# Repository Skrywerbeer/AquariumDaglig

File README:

# AquariumDaglig
This is my project for a switched solar day light. Unfortunatly I blew up my remaining LEDs so the firmware has stalled at this working version.
## Theory of Operation
TCB0 is configured in single-shot mode, the start of which is triggered by AC0's output via the event system.
When TCB0 is triggered PA6 is driven low, turning off the MOSFET allowing the inductor current to circulate
through the schottky diode and the LED string; resetting the inductor. In the main loop the PV voltage is monitored
based on it's value the reference for AC0 is either increased or decreased setting the peak inductor current.

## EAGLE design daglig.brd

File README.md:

# AquariumDaglig
This is my project for a switched solar day light. Unfortunatly I blew up my remaining LEDs so the firmware has stalled at this working version.

## Theory of Operation
TCB0 is configured in single-shot mode, the start of which is triggered by AC0's output via the event system.
When TCB0 is triggered PA6 is driven low, turning off the MOSFET allowing the inductor current to circulate
through the schottky diode and the LED string; resetting the inductor. In the main loop the PV voltage is monitored
based on it's value the reference for AC0 is either increased or decreased setting the peak inductor current.

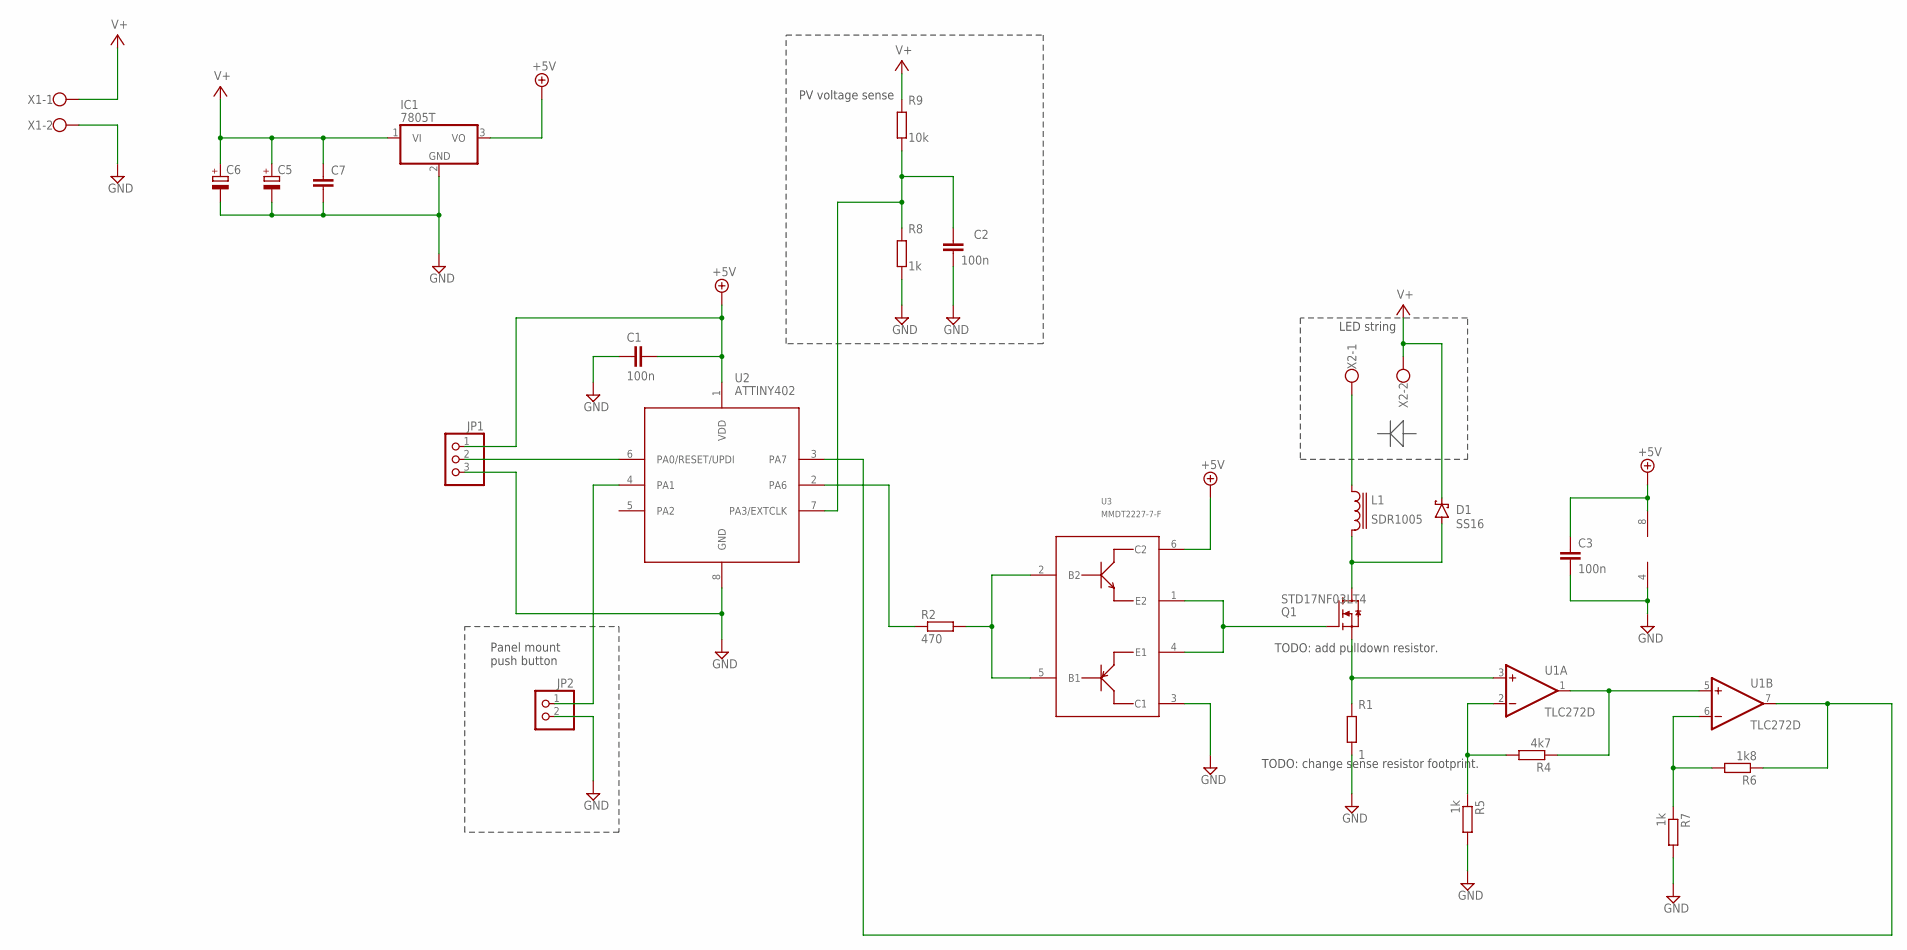
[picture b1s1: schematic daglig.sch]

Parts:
C1, C2, C3: 100n; C0805
C5, C6: CPOL-EUE5-10.5; E5-10,5
C7: C-EUC0805; C0805
D1: SS16; DO214AC
IC1: 7805T; TO220H
JP1: PINHD-1X3; 1X03
JP2: PINHD-1X2; 1X02
L1: SDR1005
Q1: STD17NF03LT4; TO252
R1: 1; R2512
R2: 470; R0805
R4: 4k7; R0805
R5, R7, R8: 1k; R0805
R6: 1k8; R0805
R9: 10k; R0805
U1: TLC272D; SO08
U2: ATTINY402; SO8
U3: MMDT2227-7-F; SOT363_PHILIPS
X1, X2: W237-102

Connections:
+5V: C1.2, C3.1, IC1.3 (VO), JP1.1, U1.8 (V+), U2.1 (VDD), U3.6 (C2)
GND: C1.1, C2.2, C3.2, C5.-, C6.-, C7.2, IC1.2 (GND), JP1.3, JP2.2, R1.1, R5.2, R7.2, R8.1, U1.4 (V-), U2.8 (GND), U3.3 (C1), X1.2
unnamed: Q1.1 (G), U3.1 (E2), U3.4 (E1)
unnamed: D1.A, L1.2, Q1.3 (D)
unnamed: R2.2, U3.2 (B2), U3.5 (B1)
unnamed: R2.1, U2.2 (PA6)
unnamed: Q1.2 (S), R1.2, U1.3 (+IN)
unnamed: R4.1, U1.1 (OUT), U1.5 (+IN)
unnamed: R6.1, U1.7 (OUT), U2.3 (PA7)
unnamed: R6.2, R7.1, U1.6 (-IN)
unnamed: R4.2, R5.1, U1.2 (-IN)
unnamed: L1.1, X2.1
unnamed: JP1.2, U2.6 (PA0/RESET/UPDI)
unnamed: C2.1, R8.2, R9.1, U2.7 (PA3/EXTCLK)
unnamed: JP2.1, U2.4 (PA1)
V+: C5.+, C6.+, C7.1, D1.C, IC1.1 (VI), R9.2, X1.1, X2.2

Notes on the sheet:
LED string
PV voltage sense
Panel mount push button
TODO: add pulldown resistor.
TODO: change sense resistor footprint.

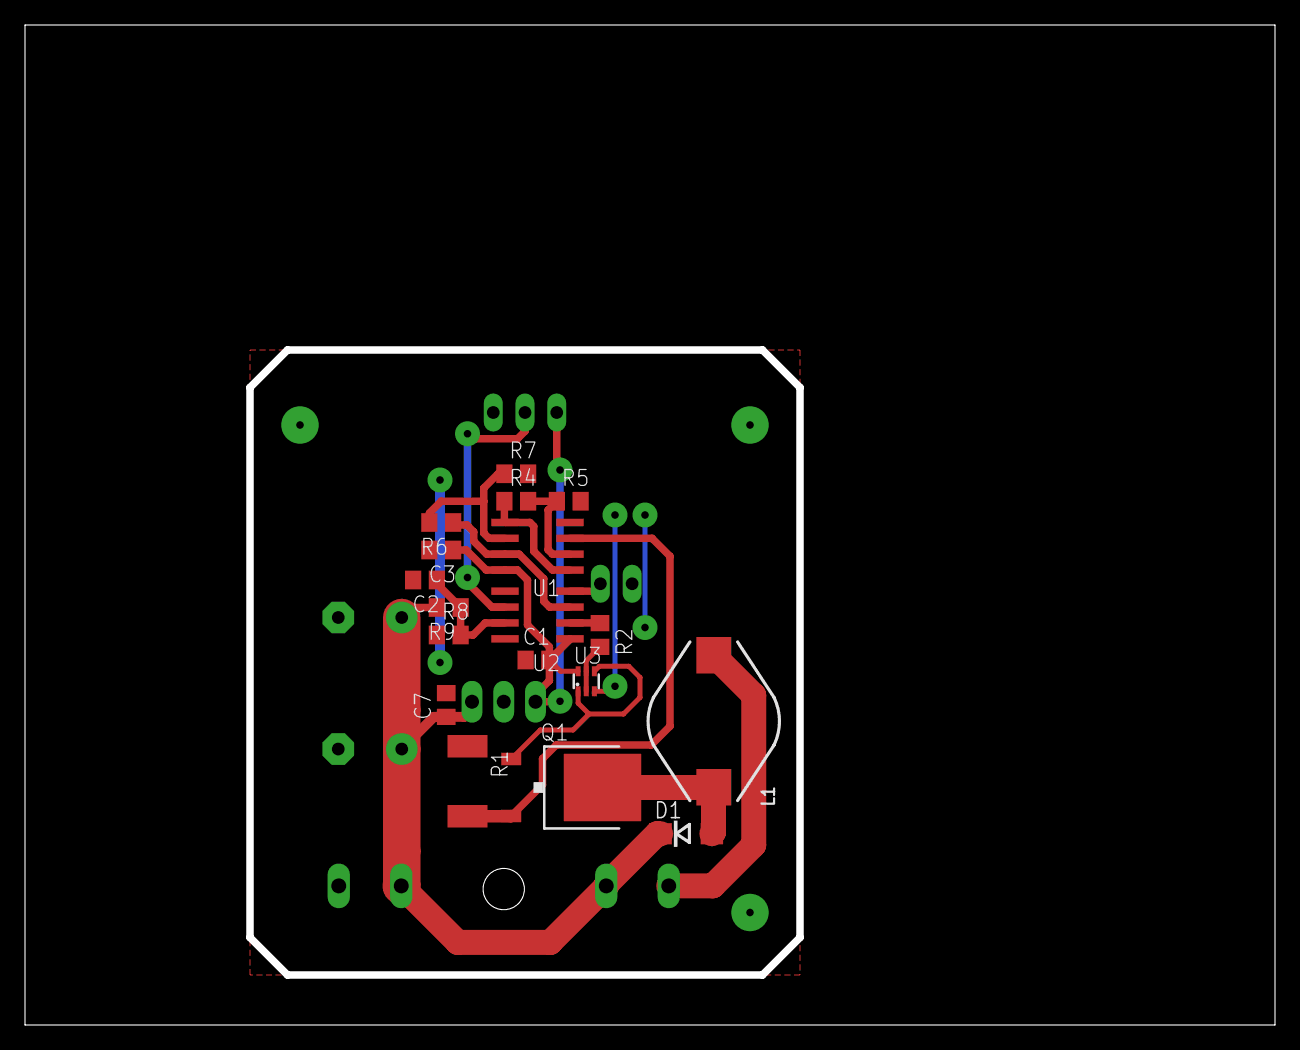
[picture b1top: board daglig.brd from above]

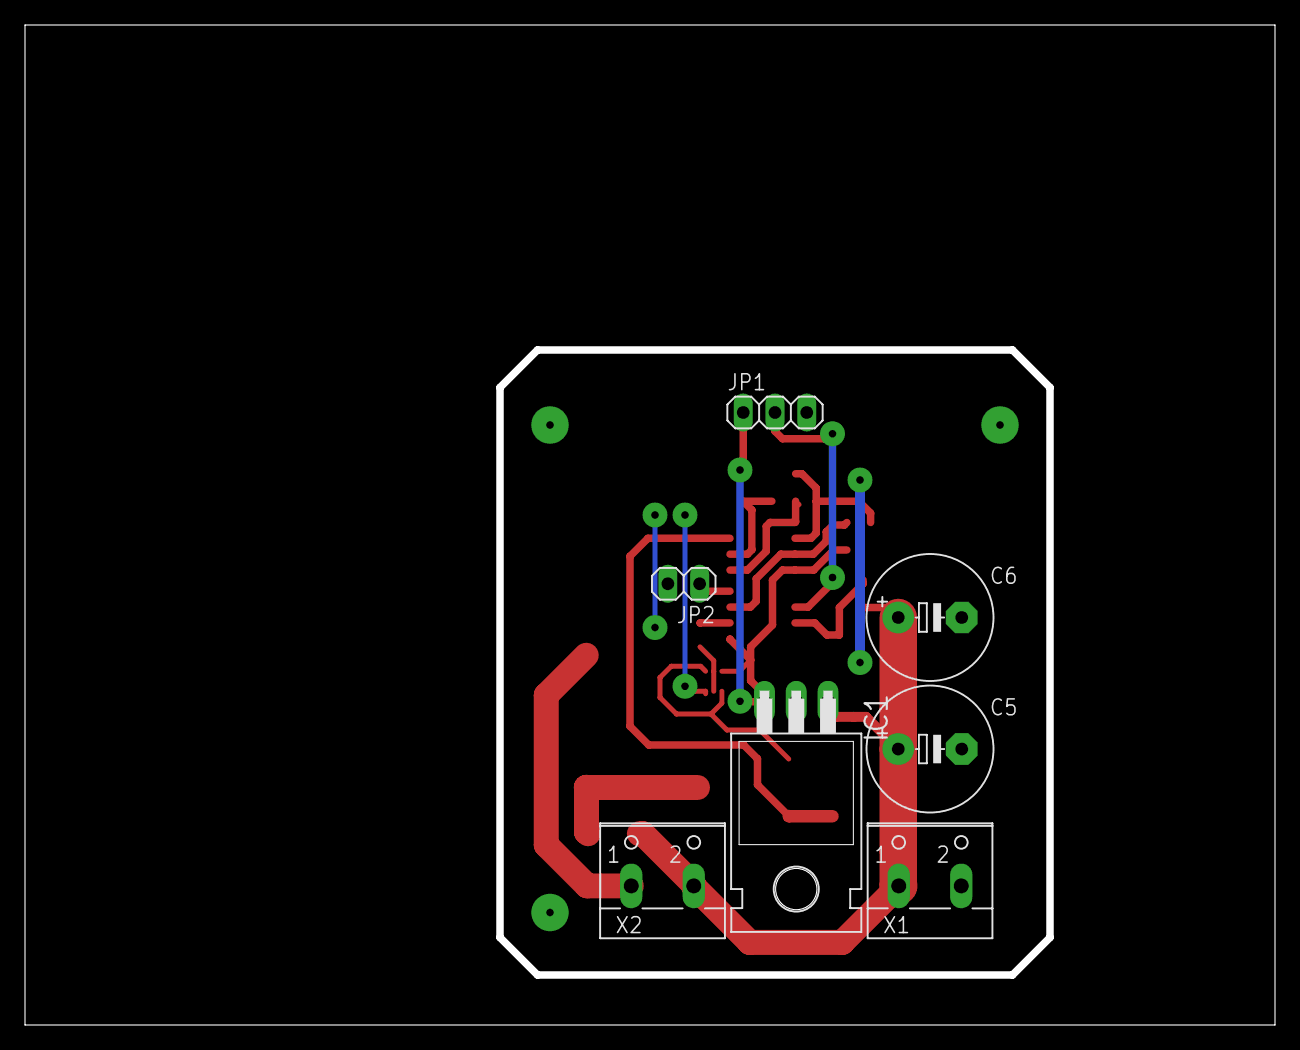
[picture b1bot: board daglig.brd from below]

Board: 2 copper layers, 99.4 x 79.4 mm, 25 parts (7 on the bottom side), 16 nets.

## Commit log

2021-10-21 Initial commit. Rev2.
2021-10-21 Cleaned up files.
2021-10-22 Further cleaning.
2021-10-25 Increased accumulated samples to sixteen.
2021-10-25 Changed deadtime to deadTime and added onTimeLimit member.
2021-10-26 Changed deadTime to offTime. TCB0 is now triggered by either TCA0 CMP0 or AC0.
2021-10-26 Back to working version.
2021-10-26 Added readme.
2021-10-26 Renamed readme
2021-10-26 Cleaned up eagle's autosaves.
2021-10-26 Added images of the boards layout and dimensions.
2021-10-26 Fixed readme.
2021-10-26 Finally fixed readme.
2021-10-26 I hoped it's really fixed now.
2021-10-26 Added todos and resistor values.

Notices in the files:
parts and their libraries:
inductor-bourns: Copyright (C) 2008, Bob Starr
